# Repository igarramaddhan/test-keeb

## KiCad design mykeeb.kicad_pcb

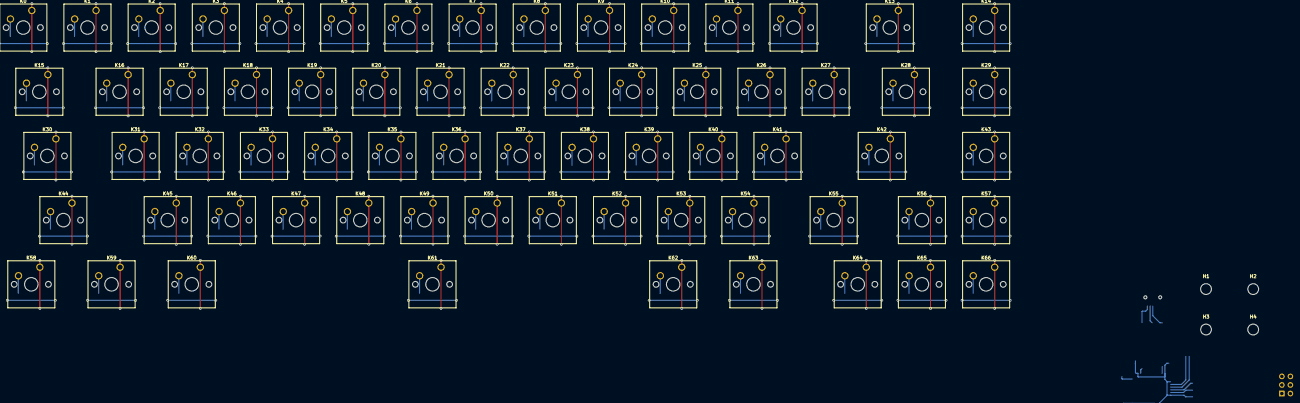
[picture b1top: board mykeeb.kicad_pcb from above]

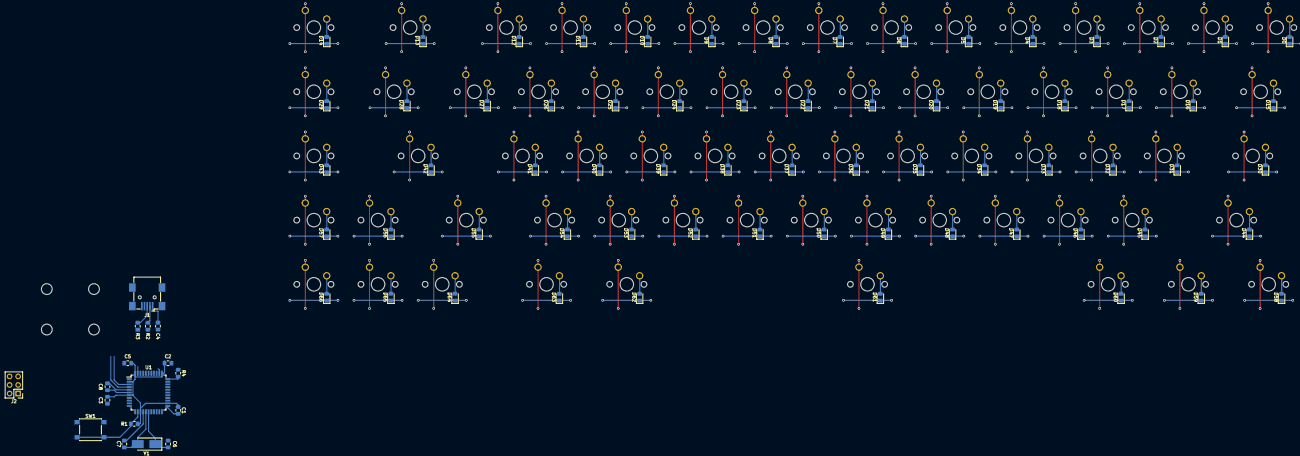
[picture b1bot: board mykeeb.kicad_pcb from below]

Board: 2 copper layers, 155 parts (84 on the bottom side), 98 nets.

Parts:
C1, C2, C3, C4: 0.1u; C_0805_2012Metric_Pad1.15x1.40mm_HandSolder
C5: 4.7u; C_0805_2012Metric_Pad1.15x1.40mm_HandSolder
C6, C7: 22p; C_0805_2012Metric_Pad1.15x1.40mm_HandSolder
C8: 1u; C_0805_2012Metric_Pad1.15x1.40mm_HandSolder
D0, D1, D2, D3, D4, D5, D6, D7, D8, D9, D10, D11, D12, D13, D14, D15, D16, D17, D18, D19, D20, D21, D22, D23, D24, D25, D26, D27, D28, D29, D30, D31, D32, D33, D34, D35, D36, D37, D38, D39, D40, D41, D42, D43, D44, D45, D46, D47, D48, D49, D50, D51, D52, D53, D54, D55, D56, D57, D58, D59, D60, D61, D62, D63, D64, D65, D66: D; D_0805_2012Metric_Pad1.15x1.40mm_HandSolder
H1, H2, H3, H4: MountingHole; MountingHole_3.2mm_M3_DIN965
J1: USB_mini_micro_B; USB_Mini-B_Wuerth_65100516121_Horizontal
J2: Conn_02x03_Odd_Even; PinHeader_2x03_P2.54mm_Vertical
K0, K1, K2, K3, K4, K5, K6, K7, K8, K9, K10, K11, K12, K14, K16, K17, K18, K19, K20, K21, K22, K23, K24, K25, K26, K27, K29, K31, K32, K33, K34, K35, K36, K37, K38, K39, K40, K41, K43, K45, K46, K47, K48, K49, K50, K51, K52, K53, K54, K56, K57, K64, K65, K66: KEYSW; SW_Cherry_MX_1.00u_PCB
K13: KEYSW; SW_Cherry_MX_2.00u_PCB
K15, K28: KEYSW; SW_Cherry_MX_1.50u_PCB
K30, K55: KEYSW; SW_Cherry_MX_1.75u_PCB
K42, K44: KEYSW; SW_Cherry_MX_2.25u_PCB
K58, K59, K60, K62, K63: KEYSW; SW_Cherry_MX_1.25u_PCB
K61: KEYSW; SW_Cherry_MX_6.25u_PCB
R1, R4: 10k; R_0805_2012Metric_Pad1.15x1.40mm_HandSolder
R2, R3: 22R; R_0805_2012Metric_Pad1.15x1.40mm_HandSolder
SW1: SW_Push; SW_Push_1P1T_NO_6x6mm_H9.5mm
U1: ATmega32U4-AU; TQFP-44_10x10mm_P0.8mm
Y1: Crystal; Crystal_SMD_5032-2Pin_5.0x3.2mm_HandSoldering

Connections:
/Col_0: K0.1, K15.1, K30.1, K44.1, K58.1, U1.32
/Col_1: K1.1, K16.1, K31.1, K45.1, K59.1, U1.31
/Col_2: K2.1, K17.1, K32.1, K46.1, K60.1, U1.30
/Col_3: K3.1, K18.1, K33.1, K47.1, K61.1, U1.29
/Col_4: K4.1, K19.1, K34.1, K48.1, K62.1, U1.28
/Col_5: K5.1, K20.1, K35.1, K49.1, K63.1, U1.27
/Col_6: K6.1, K21.1, K36.1, K50.1, K64.1, U1.26
/Col_7: K7.1, K22.1, K37.1, K51.1, K65.1, U1.25
/Col_8: K8.1, K23.1, K38.1, K52.1, K66.1, U1.36
/Col_9: K9.1, K24.1, K39.1, K53.1, U1.37
/Col_10: K10.1, K25.1, K40.1, K54.1, U1.38
/Col_11: K11.1, K26.1, K41.1, K55.1, U1.39
/Col_12: K12.1, K27.1, K42.1, K56.1, U1.40
/Col_13: K13.1, K28.1, K43.1, K57.1, U1.41
/Col_14: K14.1, K29.1, U1.22
/Row_0: D0.1, D1.1, D2.1, D3.1, D4.1, D5.1, D6.1, D7.1, D8.1, D9.1, D10.1, D11.1, D12.1, D13.1, D14.1, U1.18
/Row_1: D15.1, D16.1, D17.1, D18.1, D19.1, D20.1, D21.1, D22.1, D23.1, D24.1, D25.1, D26.1, D27.1, D28.1, D29.1, U1.12
/Row_2: D30.1, D31.1, D32.1, D33.1, D34.1, D35.1, D36.1, D37.1, D38.1, D39.1, D40.1, D41.1, D42.1, D43.1, J2.2, U1.11
/Row_3: D44.1, D45.1, D46.1, D47.1, D48.1, D49.1, D50.1, D51.1, D52.1, D53.1, D54.1, D55.1, D56.1, D57.1, J2.4, U1.10
/Row_4: D58.1, D59.1, D60.1, D61.1, D62.1, D63.1, D64.1, D65.1, D66.1, J2.3, U1.9
GND: C1.2, C2.2, C3.2, C4.2, C5.2, C6.2, C7.2, C8.2, J1.5, J1.6, J2.5, R4.1, SW1.1, U1.5, U1.15, U1.23, U1.35, U1.43
unnamed: C6.1, U1.17, Y1.1
unnamed: C7.1, U1.16, Y1.2
unnamed: C8.1, U1.6
unnamed: D0.2, K0.2
unnamed: D1.2, K1.2
unnamed: D2.2, K2.2
unnamed: D3.2, K3.2
unnamed: D4.2, K4.2
unnamed: D5.2, K5.2
unnamed: D6.2, K6.2
unnamed: D7.2, K7.2
unnamed: D8.2, K8.2
unnamed: D9.2, K9.2
unnamed: D10.2, K10.2
unnamed: D11.2, K11.2
unnamed: D12.2, K12.2
unnamed: D13.2, K13.2
unnamed: D14.2, K14.2
unnamed: D15.2, K15.2
unnamed: D16.2, K16.2
unnamed: D17.2, K17.2
unnamed: D18.2, K18.2
unnamed: D19.2, K19.2
unnamed: D20.2, K20.2
unnamed: D21.2, K21.2
unnamed: D22.2, K22.2
unnamed: D23.2, K23.2
unnamed: D24.2, K24.2
unnamed: D25.2, K25.2
unnamed: D26.2, K26.2
unnamed: D27.2, K27.2
unnamed: D28.2, K28.2
unnamed: D29.2, K29.2
unnamed: D30.2, K30.2
unnamed: D31.2, K31.2
unnamed: D32.2, K32.2
unnamed: D33.2, K33.2
unnamed: D34.2, K34.2
unnamed: D35.2, K35.2
unnamed: D36.2, K36.2
unnamed: D37.2, K37.2
unnamed: D38.2, K38.2
unnamed: D39.2, K39.2
unnamed: D40.2, K40.2
unnamed: D41.2, K41.2
unnamed: D42.2, K42.2
unnamed: D43.2, K43.2
unnamed: D44.2, K44.2
unnamed: D45.2, K45.2
unnamed: D46.2, K46.2
unnamed: D47.2, K47.2
unnamed: D48.2, K48.2
unnamed: D49.2, K49.2
unnamed: D50.2, K50.2
unnamed: D51.2, K51.2
unnamed: D52.2, K52.2
unnamed: D53.2, K53.2
unnamed: D54.2, K54.2
unnamed: D55.2, K55.2
unnamed: D56.2, K56.2
unnamed: D57.2, K57.2
unnamed: D58.2, K58.2
unnamed: D59.2, K59.2
unnamed: D60.2, K60.2
unnamed: D61.2, K61.2
unnamed: D62.2, K62.2
unnamed: D63.2, K63.2
unnamed: D64.2, K64.2
unnamed: D65.2, K65.2
unnamed: D66.2, K66.2
unnamed: J1.2, R2.2
unnamed: J1.3, R3.2
unnamed: R1.1, SW1.2, U1.13
unnamed: R2.1, U1.4
unnamed: R3.1, U1.3
unnamed: R4.2, U1.33
VCC: C1.1, C2.1, C3.1, C4.1, C5.1, J1.1, J2.1, R1.2, U1.2, U1.7, U1.14, U1.24, U1.34, U1.44
